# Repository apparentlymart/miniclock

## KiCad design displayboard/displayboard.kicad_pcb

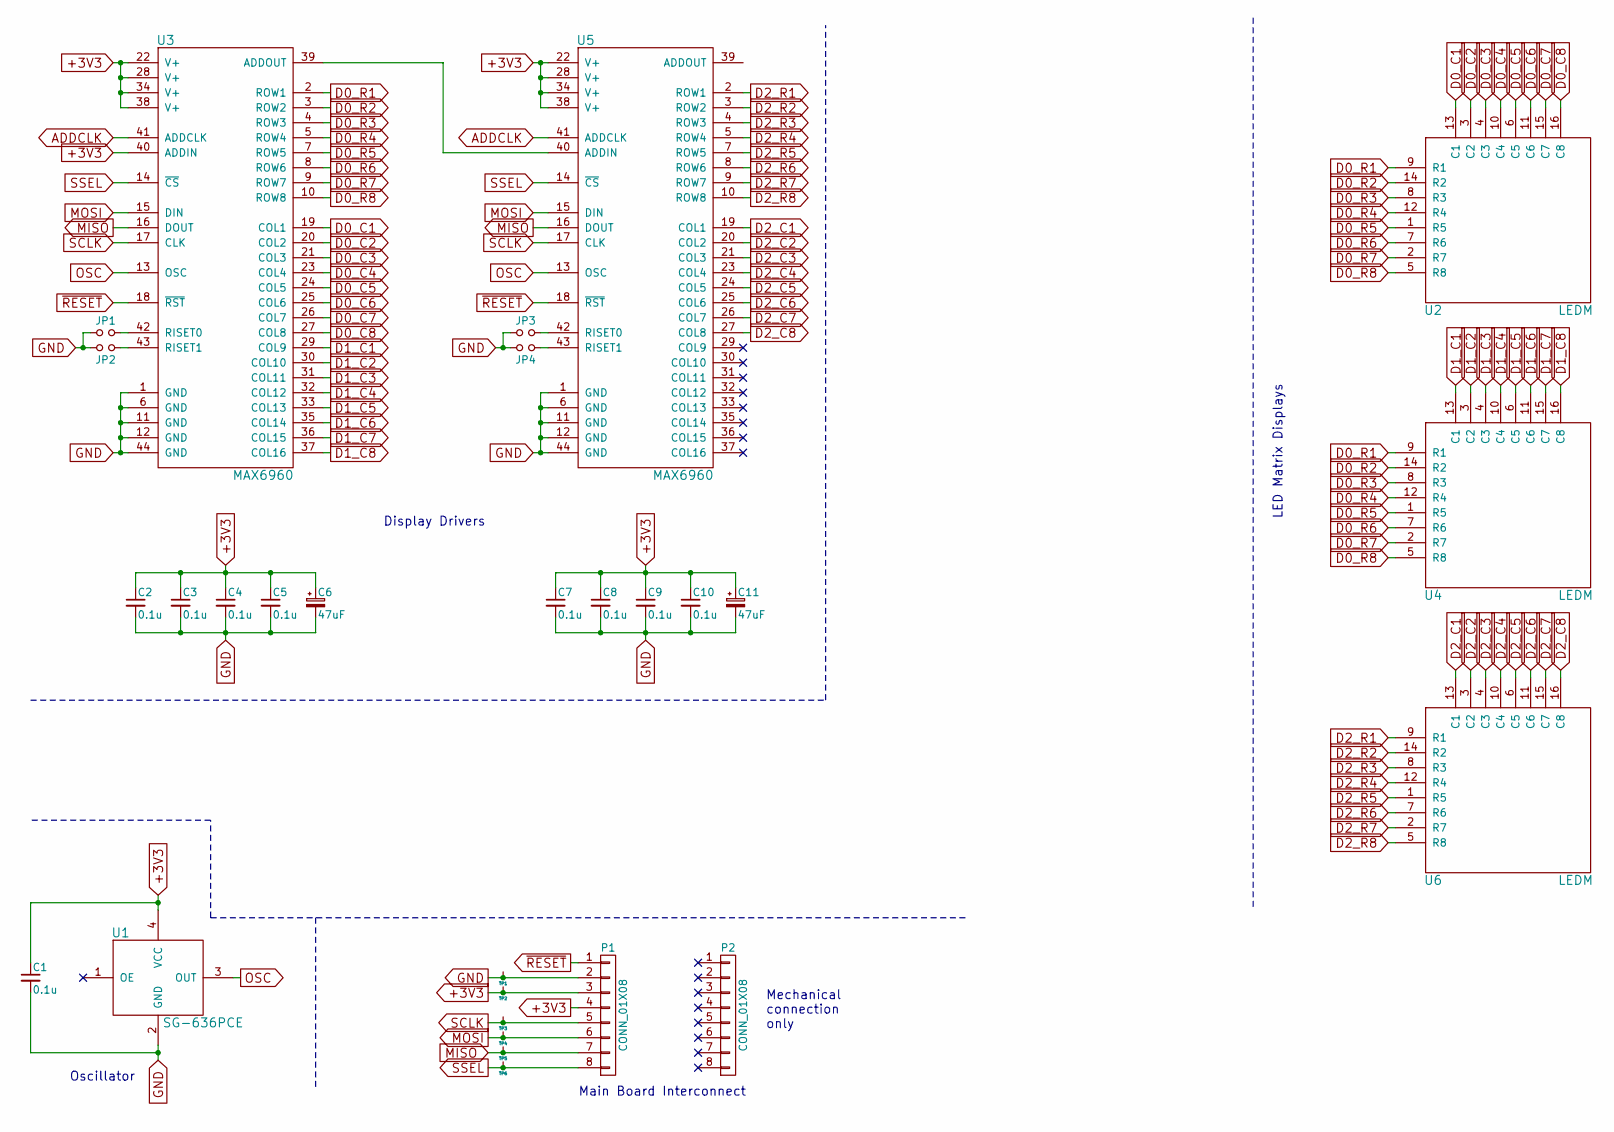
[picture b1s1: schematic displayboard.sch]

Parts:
C1, C2, C3, C4, C5, C7, C8, C9, C10: 0.1u; 0805
C6, C11: 47uF; UWX1V470MCL1GB
JP1, JP2, JP3, JP4: Jumper_NO_Small; 0805
P1, P2: CONN_01X08; Pin_Header_Straight_1x08
TP1, TP2, TP3, TP4, TP5, TP6: TESTPOINT
U1: SG-636PCE
U2, U4, U6: LEDM; KWM-R30881CUYB
U3, U5: MAX6960

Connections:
+3V3: C1.1, C2.1, C3.1, C4.1, C5.1, C6.1, C7.1, C8.1, C9.1, C10.1, C11.1, P1.3, P1.4, TP2.1, U1.4 (VCC), U3.22 (V+), U3.28 (V+), U3.34 (V+), U3.38 (V+), U3.40 (ADDIN), U5.22 (V+), U5.28 (V+), U5.34 (V+), U5.38 (V+)
ADDCLK: U3.41 (ADDCLK), U5.41 (ADDCLK)
D0_C1: U2.13 (C1), U3.19 (COL1)
D0_C2: U2.3 (C2), U3.20 (COL2)
D0_C3: U2.4 (C3), U3.21 (COL3)
D0_C4: U2.10 (C4), U3.23 (COL4)
D0_C5: U2.6 (C5), U3.24 (COL5)
D0_C6: U2.11 (C6), U3.25 (COL6)
D0_C7: U2.15 (C7), U3.26 (COL7)
D0_C8: U2.16 (C8), U3.27 (COL8)
D0_R1: U2.9 (R1), U3.2 (ROW1), U4.9 (R1)
D0_R2: U2.14 (R2), U3.3 (ROW2), U4.14 (R2)
D0_R3: U2.8 (R3), U3.4 (ROW3), U4.8 (R3)
D0_R4: U2.12 (R4), U3.5 (ROW4), U4.12 (R4)
D0_R5: U2.1 (R5), U3.7 (ROW5), U4.1 (R5)
D0_R6: U2.7 (R6), U3.8 (ROW6), U4.7 (R6)
D0_R7: U2.2 (R7), U3.9 (ROW7), U4.2 (R7)
D0_R8: U2.5 (R8), U3.10 (ROW8), U4.5 (R8)
D1_C1: U3.29 (COL9), U4.13 (C1)
D1_C2: U3.30 (COL10), U4.3 (C2)
D1_C3: U3.31 (COL11), U4.4 (C3)
D1_C4: U3.32 (COL12), U4.10 (C4)
D1_C5: U3.33 (COL13), U4.6 (C5)
D1_C6: U3.35 (COL14), U4.11 (C6)
D1_C7: U3.36 (COL15), U4.15 (C7)
D1_C8: U3.37 (COL16), U4.16 (C8)
D2_C1: U5.19 (COL1), U6.13 (C1)
D2_C2: U5.20 (COL2), U6.3 (C2)
D2_C3: U5.21 (COL3), U6.4 (C3)
D2_C4: U5.23 (COL4), U6.10 (C4)
D2_C5: U5.24 (COL5), U6.6 (C5)
D2_C6: U5.25 (COL6), U6.11 (C6)
D2_C7: U5.26 (COL7), U6.15 (C7)
D2_C8: U5.27 (COL8), U6.16 (C8)
D2_R1: U5.2 (ROW1), U6.9 (R1)
D2_R2: U5.3 (ROW2), U6.14 (R2)
D2_R3: U5.4 (ROW3), U6.8 (R3)
D2_R4: U5.5 (ROW4), U6.12 (R4)
D2_R5: U5.7 (ROW5), U6.1 (R5)
D2_R6: U5.8 (ROW6), U6.7 (R6)
D2_R7: U5.9 (ROW7), U6.2 (R7)
D2_R8: U5.10 (ROW8), U6.5 (R8)
GND: C1.2, C2.2, C3.2, C4.2, C5.2, C6.2, C7.2, C8.2, C9.2, C10.2, C11.2, JP1.1, JP2.2, JP3.1, JP4.2, P1.2, TP1.1, U1.2 (GND), U3.1 (GND), U3.6 (GND), U3.11 (GND), U3.12 (GND), U3.44 (GND), U5.1 (GND), U5.6 (GND), U5.11 (GND), U5.12 (GND), U5.44 (GND)
MISO: P1.7, TP5.1, U3.16 (DOUT), U5.16 (DOUT)
MOSI: P1.6, TP4.1, U3.15 (DIN), U5.15 (DIN)
unnamed: JP1.2, U3.42 (RISET0)
unnamed: JP2.1, U3.43 (RISET1)
unnamed: JP3.2, U5.42 (RISET0)
unnamed: JP4.1, U5.43 (RISET1)
unnamed: U3.39 (ADDOUT), U5.40 (ADDIN)
OSC: U1.3 (OUT), U3.13 (OSC), U5.13 (OSC)
SCLK: P1.5, TP3.1, U3.17 (CLK), U5.17 (CLK)
SSEL: P1.8, TP6.1, U3.14 (~CS), U5.14 (~CS)
~RESET: P1.1, U3.18 (~RST), U5.18 (~RST)

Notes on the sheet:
Mechanical connection only
Main Board Interconnect
Oscillator
LED Matrix Displays
Display Drivers

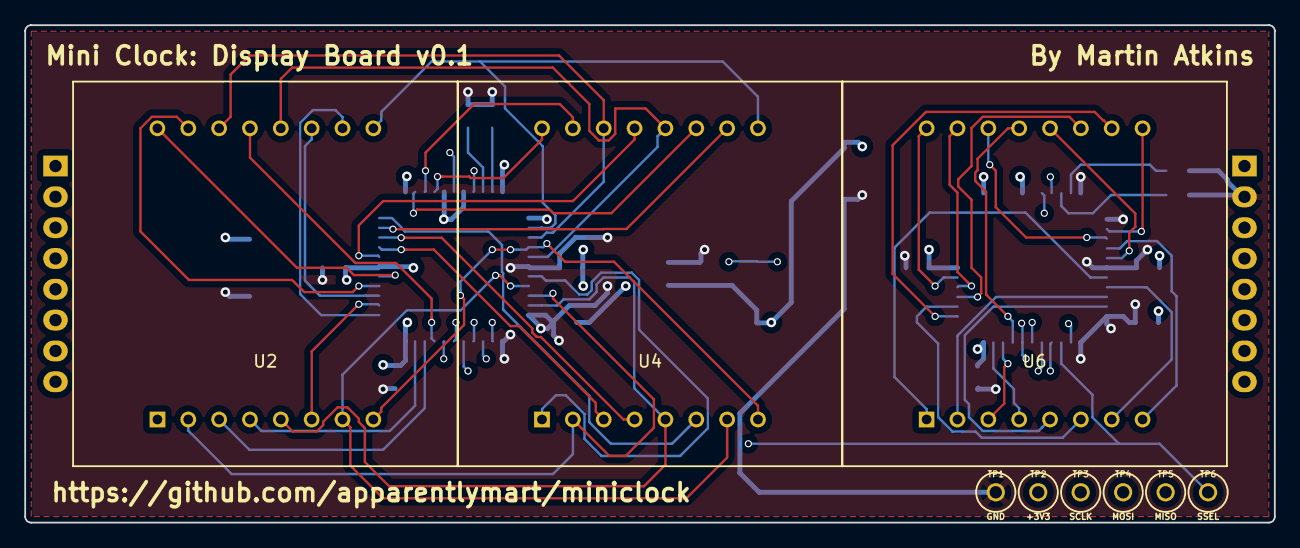
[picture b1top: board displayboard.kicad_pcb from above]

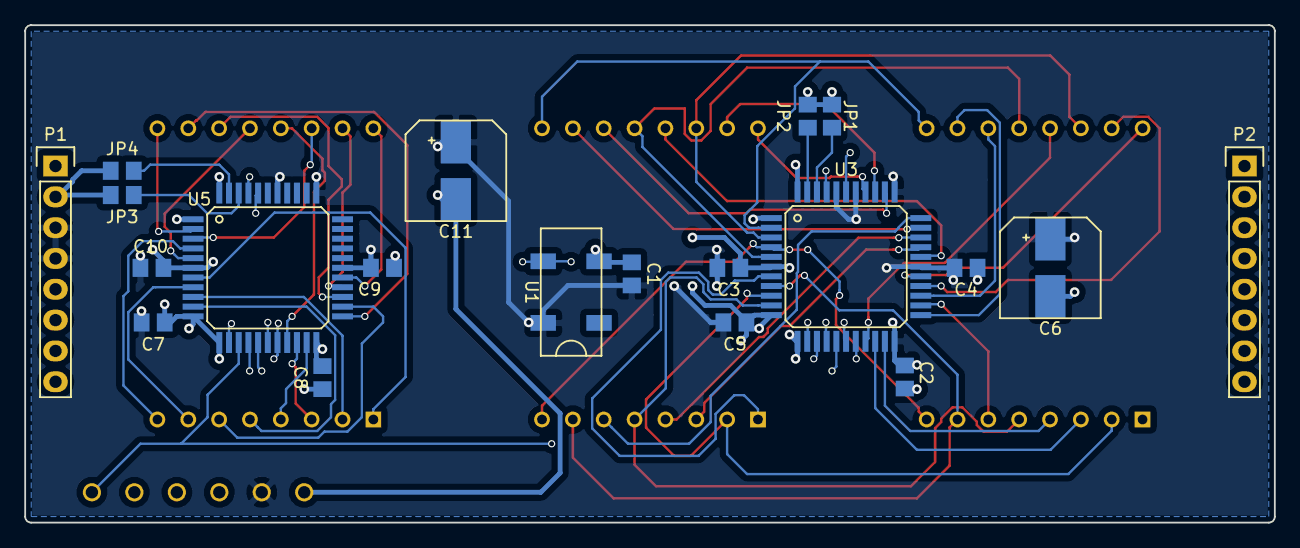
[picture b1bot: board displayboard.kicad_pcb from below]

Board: 4 copper layers, 103.0 x 41.0 mm, 29 parts (20 on the bottom side), 54 nets.

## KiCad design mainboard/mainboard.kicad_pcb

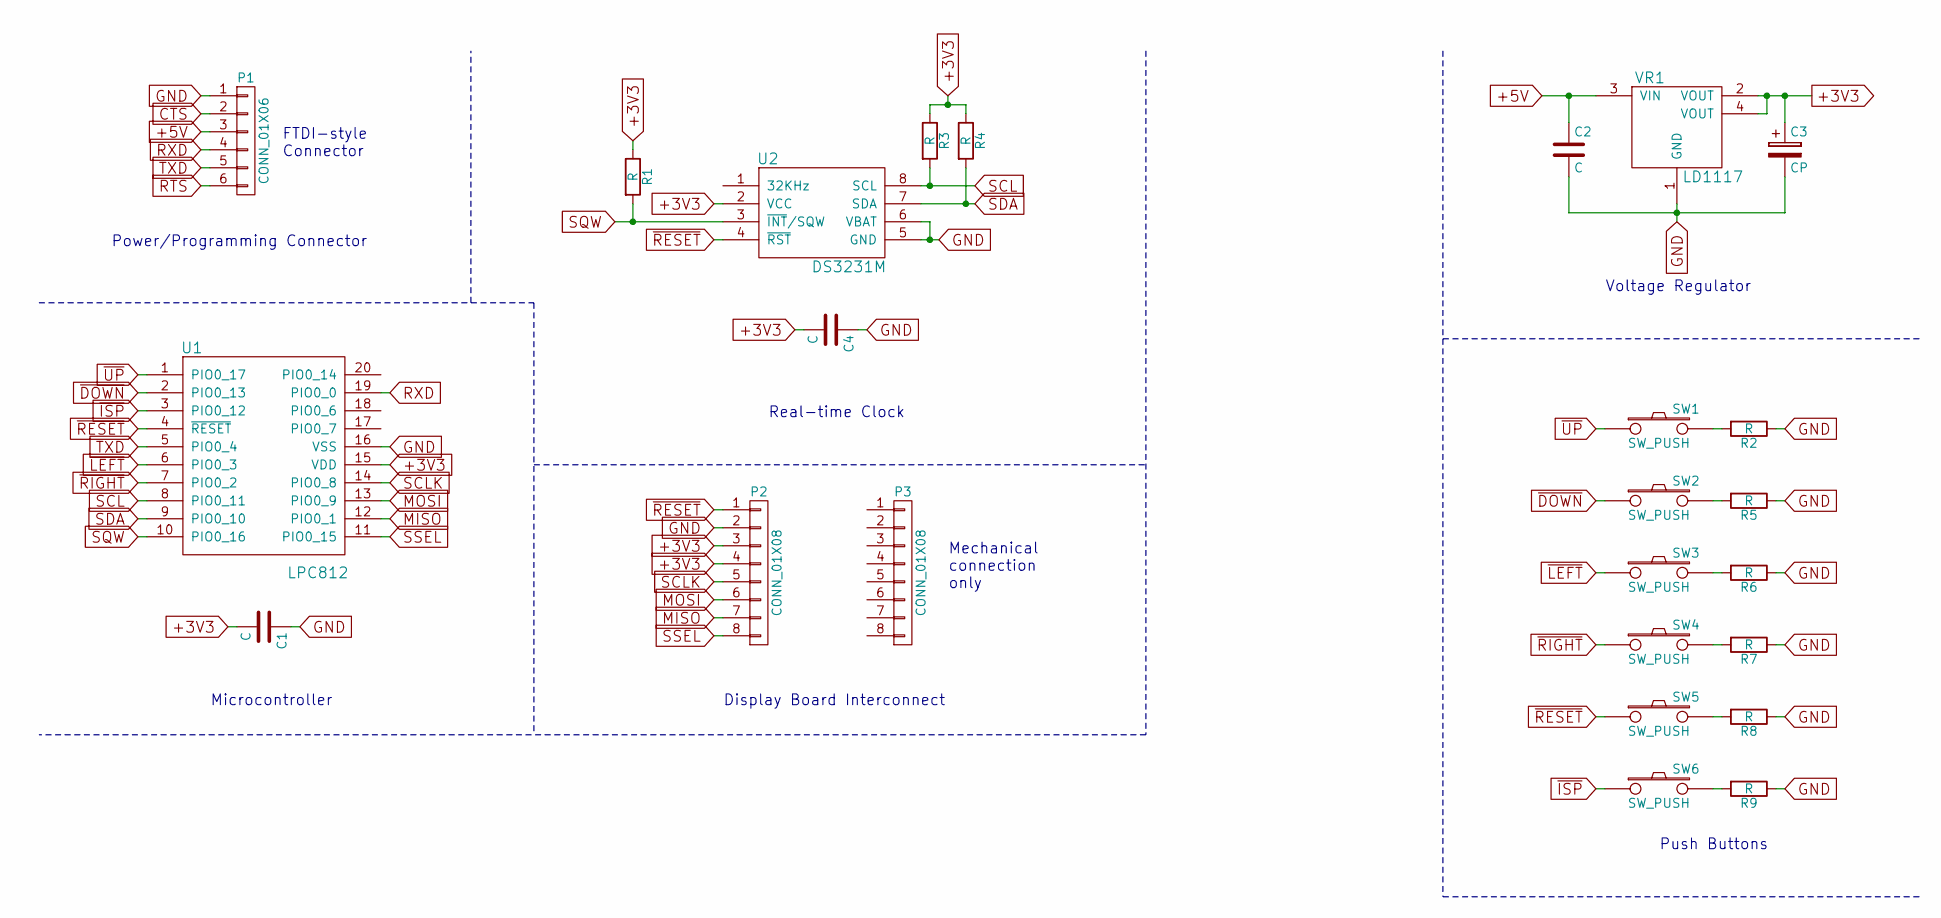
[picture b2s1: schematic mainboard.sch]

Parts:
C1, C2, C4: C; C_0805_HandSoldering
C3: CP; CPOL_SMD_6.3mm
P1: CONN_01X06; Pin_Header_Straight_1x06
P2, P3: CONN_01X08; Pin_Header_Straight_1x08
R1, R2, R3, R4, R5, R6, R7, R8, R9: R; R_0805_HandSoldering
SW1, SW2, SW3, SW4, SW5, SW6: SW_PUSH; PUSHSWITCH
U1: LPC812; SOIC-20_7.5x12.8mm_Pitch1.27mm
U2: DS3231M; SOIC-8_3.9x4.9mm_Pitch1.27mm
VR1: LD1117; SOT223

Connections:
+3V3: C1.2, C3.1, C4.2, P2.3, P2.4, R1.1, R3.1, R4.1, U1.15 (VDD), U2.2 (VCC), VR1.2 (VOUT), VR1.4 (VOUT)
+5V: C2.1, P1.3, VR1.3 (VIN)
CTS: P1.2
GND: C1.1, C2.2, C3.2, C4.1, P1.1, P2.2, R2.1, R5.1, R6.1, R7.1, R8.1, R9.1, U1.16 (VSS), U2.5 (GND), U2.6 (VBAT), VR1.1 (GND)
MISO: P2.7, U1.12 (PIO0_1)
MOSI: P2.6, U1.13 (PIO0_9)
unnamed: R2.2, SW1.2
unnamed: R5.2, SW2.2
unnamed: R6.2, SW3.2
unnamed: R7.2, SW4.2
unnamed: R8.2, SW5.2
unnamed: R9.2, SW6.2
RTS: P1.6
RXD: P1.4, U1.19 (PIO0_0)
SCL: R3.2, U1.8 (PIO0_11), U2.8 (SCL)
SCLK: P2.5, U1.14 (PIO0_8)
SDA: R4.2, U1.9 (PIO0_10), U2.7 (SDA)
SQW: R1.2, U1.10 (PIO0_16), U2.3 (~INT~/SQW)
SSEL: P2.8, U1.11 (PIO0_15)
TXD: P1.5, U1.5 (PIO0_4)
~DOWN: SW2.1, U1.2 (PIO0_13)
~ISP: SW6.1, U1.3 (PIO0_12)
~LEFT: SW3.1, U1.6 (PIO0_3)
~RESET: P2.1, SW5.1, U1.4 (~RESET), U2.4 (~RST)
~RIGHT: SW4.1, U1.7 (PIO0_2)
~UP: SW1.1, U1.1 (PIO0_17)

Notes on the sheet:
FTDI-style Connector
Microcontroller
Real-time Clock
Voltage Regulator
Power/Programming Connector
Mechanical connection only
Display Board Interconnect
Push Buttons

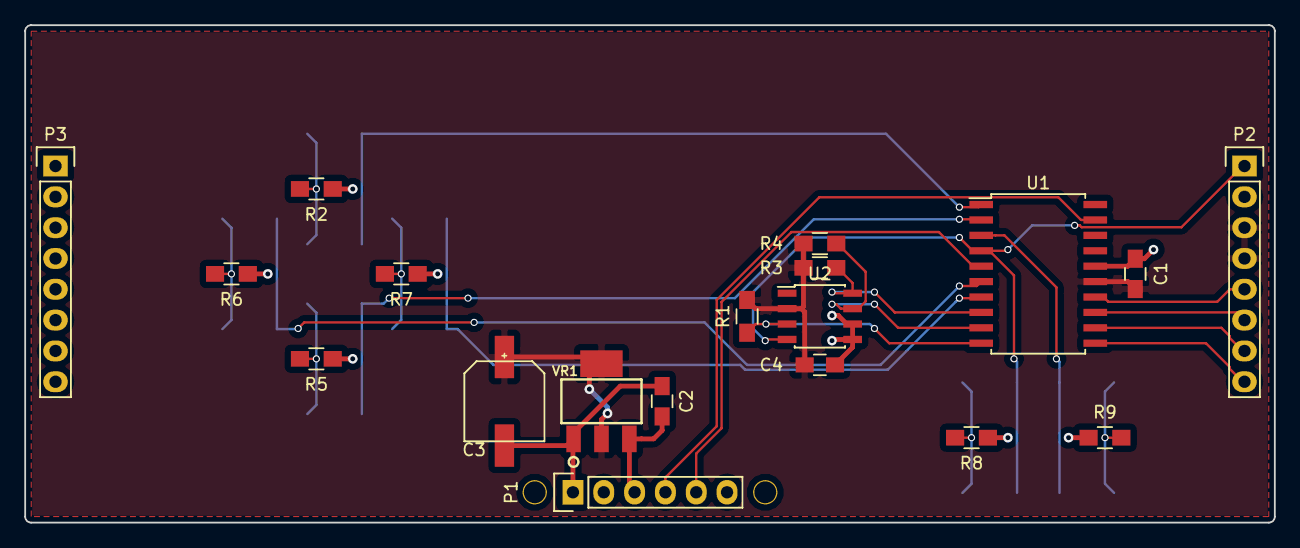
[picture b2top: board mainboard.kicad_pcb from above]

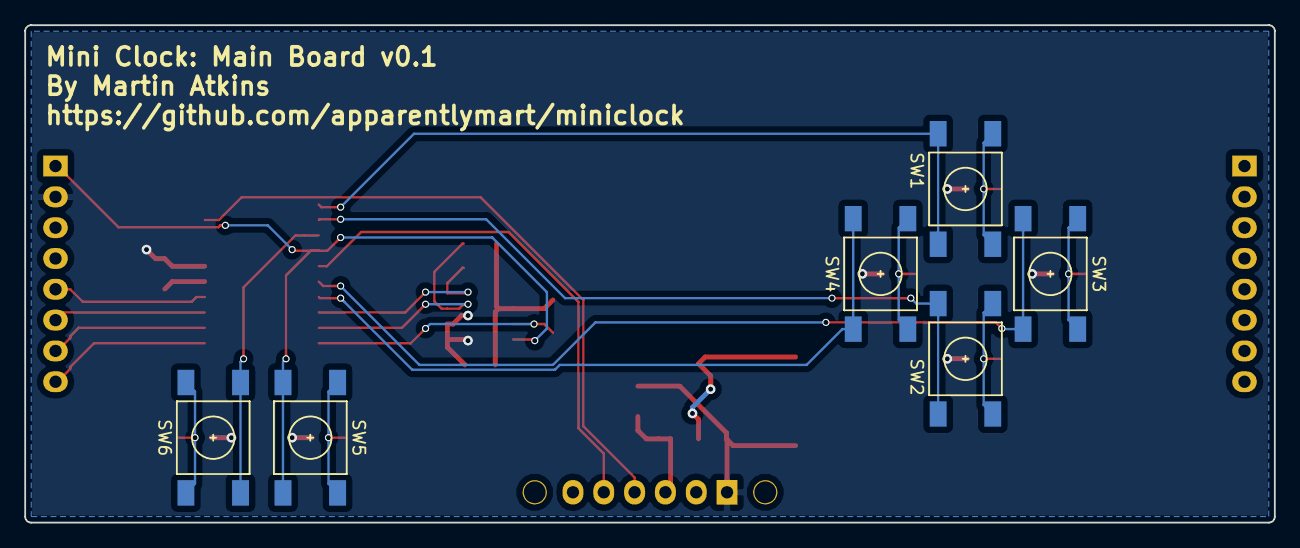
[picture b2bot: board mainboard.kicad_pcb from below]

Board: 2 copper layers, 103.0 x 41.0 mm, 25 parts (6 on the bottom side), 24 nets.

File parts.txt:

RTC:
http://www.digikey.com/product-detail/en/DS3231MZ%2B/DS3231M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

LPC812 Microcontroller:
http://www.digikey.com/product-detail/en/LPC812M101JD20FP/56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

Right-angle header (for FTDI serial cable):
http://www.digikey.com/product-detail/en/0901210126/WM8100-N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

Square 1.2" LED matrix:
http://www.adafruit.com/products/1819

LED Matrix Driver
http://www.digikey.com/product-detail/en/MAX6960AMH%2BD/MAX6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

3.3V voltage regulator
http://www.digikey.com/product-detail/en/LD1117S33TR/497-124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

6 Buttons:
http://www.digikey.com/product-detail/en/FSM4JSMATR/450-1759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

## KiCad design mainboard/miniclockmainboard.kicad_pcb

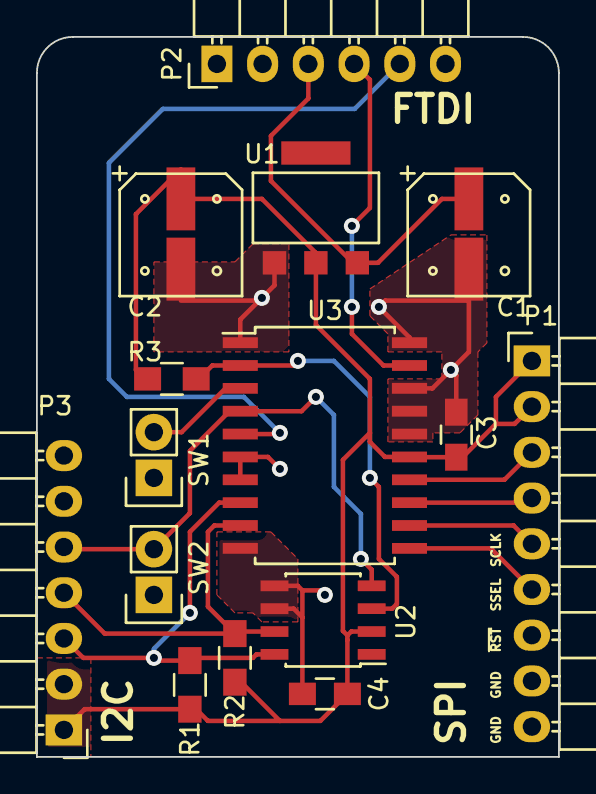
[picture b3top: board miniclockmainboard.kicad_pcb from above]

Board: 2 copper layers, 29.0 x 40.0 mm, 15 parts (0 on the bottom side), 14 nets.

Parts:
C1, C2: 10uF; Nichicon_PolCap_6.3
C3, C4: 0.1uF; C_0805_HandSoldering
P1: CONN_9; Pin_Header_Angled_1x09
P2: CONN_6; Pin_Header_Angled_1x06
P3: CONN_7; Pin_Header_Angled_1x07
R1, R2, R3: 10k; R_0805_HandSoldering
SW1, SW2: SW_PUSH; Pin_Header_Straight_1x02
U1: LD1117; SOT-223
U2: DS3231M; SOIC-8_3.9x4.9mm_Pitch1.27mm
U3: LPC812M101JD20; SOIC-20_7.5x12.8mm_Pitch1.27mm

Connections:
/1HZ: R3.2, U2.3, U3.2
/+5V: C1.1, P2.3, U1.3
/MISO: P1.4, U3.13
/MOSI: P1.3, U3.14
/RXD: P2.5, U3.5
/SCL: P3.3, R1.2, U2.8, U3.8
/SCLK: P1.5, U3.12
/SDA: P3.4, R2.2, U2.7, U3.9
/SSEL: P1.6, U3.11
/TXD: P2.4, U3.19
/~RST: P1.7, P3.5, SW2.2, U2.4, U3.4
GND: C1.2, C2.2, C3.2, C4.1, P1.8, P1.9, P2.1, P3.6, P3.7, SW1.1, SW2.1, U1.1, U2.5, U2.6, U3.1, U3.6, U3.7, U3.10, U3.16, U3.17, U3.18, U3.20
unnamed: SW1.2, U3.3
VCC: C2.1, C3.1, C4.2, P1.1, P1.2, P3.1, P3.2, R1.1, R2.1, R3.1, U1.2, U2.2, U3.15

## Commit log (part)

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2015-02-23 Sketch BOM
2015-02-28 Update the parts list.
2015-02-28 KiCAD project.
2015-02-28 Initial import of schematic, with voltage regulator.
2015-02-28 Basic wiring for MCU and RTC.
    Still need to add capacitors to the power inputs.
2015-03-28 Local eeschema library, starting with LCP812 symbol.
2015-03-28 Start of schematic for the main control board.
2015-03-28 Further work on the main board schematic.
2015-03-28 Complete first rev of the main board schematic.
2015-03-28 Some PCB footprints for the main board.
2015-03-28 Schematic to footprint mappings.
2015-03-28 Main board PCB layout.
2015-03-28 Add some silkscreen captions to the rear of the main board.
2015-03-29 Shrink the main board width.
    Previous version was slightly too wide for the first prototype's
    enclosure. The new size is much smaller than the available space in the
    enclosure.
2015-03-29 Fix up the pad positions on the polarized caps.
    The pads were incorrectly spaced before since the space between the pad
    edges was confused with the space between the centers.
2015-09-08 Delete everything so we can start over.
    This project has bitrotted since I last opened it, so rather than trying
    to repair it I'm just going to start over again.
2015-09-08 Map schematic symbols to footprints.
2015-09-08 Mainboard outline
2015-09-08 Component placement on PCB.
2015-09-08 Random schematic editor settings.
2015-09-08 DC regulator traces.
2015-09-08 Button traces.
2015-09-08 RTC traces.
2015-09-08 Remaining traces.
2015-09-08 Connect final missing link.
    (This isn't actually really needed since these things are connected
    internally within the regulator, but this pacifies the KiCad DRC.
2015-09-08 Using a larger LED matrix now.
    Going bigger because it'll be easier to fit the LED matrix drivers on the
    display board this way. It isn't really necessary for the mainboard to be
    this large except that it ought to match the display board.
2015-10-18 First steps towards a firmware.
    This builds and runs but doesn't quite work yet... the UART seems to be
    running faster than desired, causing every alternating character to be
    missed by the receiving device.
2015-10-26 Don't run lpc21isp with sudo.
    Now got udev rules set up properly for this, so don't need it on my
    machine and it's a bad idea in general anyway.
2015-10-26 Header guards on lpc812.h and serial.h.
2015-10-26 Use the PLL for the main clock.
    This allows us to run at 60MHz.
2015-10-26 Print newline at the end of our message.
2015-10-26 Poll indefinitely for USART RX to become available.
    Also wait for it to return to idle after each character. This isn't
    strictly necessary but it keeps things easier for debugging for the
    moment.
2015-10-30 Explicitly set the system clock to 60MHz.
    In spite of the earlier comment to the contrary, this was actually already
    the case because that's the boot-time setting. Here we just correct the
    comment and add an explicit configuration to aid in understanding of
    what's going on here.
2015-10-30 Correctly configure the UART.
    Some mis-reading of the datasheet led to a complete misunderstanding of
    the structure of the USART0_CFG register, causing the UART to be
    configured for 2 stop bits, 7-bit data length and even parity. Despite
    how wrong this was, it ended up generating a bunch of bytes correctly,
    making it hard at first to recognize the problem.
    The new setting is, as the comment originally suggested, 1 stop bit,
2015-11-02 Basic prototype of using pin interrupts.
    Still doesn't do anything useful, but this is a reasonable checkpoint
    on the way to having a button driver.
2015-11-06 Use C11 standard when compiling.
2015-11-06 Use udev alias /dev/miniclock for programming.
2015-11-06 Blocking I2C driver.
    Will rewrite this to be interrupt-driven later, but this is just a simple
    case to prove that the RTC chip is behaving.
2015-11-06 Sleep and use the RTC's 1Hz square wave to wake up every 0.5s.
    Still just more prototyping, in this case making sure that we can use the
    1Hz SQW pin as an interrupt and sleep between them.
2015-11-06 Start stubbing out the scheduler interface.
2015-11-08 Link with gcc so we can include libgcc.
2015-11-08 Add some interrupt vectors that were skipped.
    All of the interrupt vectors above 12 were off by three, which explains
    why the GPIO interrupts didn't seem to be working quite right before.
2015-11-08 Wake-up timer registers.
2015-11-08 PMU registers.
2015-11-08 Fleshed out scheduler.
    It now basically works and supports timer events. It's using the
    SysTick timer, so we run through the event loop at least once every
    10ms.
    Ideally we would set the timer to occur at the time of the next timer
    in the list, but so far I couldn't find a way to measure the time
    elapsed while the processor is asleep and so waking up every 10ms is
2015-11-08 Timer task list should be in order of wake_time.
    Previously I cheated and just appended each new task to the end of the
    list, since I knew the test code only had one task at a time. This is the
    more correct implementation, inserting the new task into the appropriate
    place in the list.
2015-11-08 Use macros to make task implementations less verbose.
    This borrows from Adam Dunkels' protothreads, but using the GCC computed
    goto extension to avoid the limitations around using switch statements.
2015-11-08 uart_println_int_hex wrapper to print a captioned integer.
2015-11-08 UI state machine represented as a DOT graph.
2015-11-09 UI state machine.
    Handles the transitions between the UI states when the directional buttons
    are pressed.
2015-11-09 Put the ui_state enum in the header, not the module.
2015-11-09 Start of display-handling code.
    The display module is responsible for rendering something appropriate
    on the screen for the current state, and creating animated transitions
    between states.
2015-11-09 Don't lock up when multiple timer tasks are outstanding.
    This loop was broken in that it would lock up if it needed to insert
    a new task after an existing task, because the loop iteration expression
    was incorrect.
2015-11-09 Export the millis count for use in other modules.
2015-11-09 Remove incorrect comment about deadlock.
    This claimed that having no runnable tasks was a deadlock, but that's
    incorrect: no runnable tasks can just mean that we're waiting for events
    to occur before any tasks become runnable.
2015-11-09 Further progress on the transition animations.
2015-11-09 Prototype display driver.
    The display is built from "display elements", which are defined by a
    row generator function and an integer argument to provide to it. Each
    element can generate zero or more display rows (which will actually be
    columns on the final display).
    Eventually each UI state will have its own set of display elements that
    together define what is displayed on-screen in that state. The display
2015-11-14 Render both states when transitioning horizontally.
2015-11-14 Vertical transitions
2015-11-14 Generalize the offset animation to work in all directions.
    The previous prototype had a separate-but-largely-identical implementation
    for each movement direction. Here we generalize this to a single
    implementation that just shifts the offset towards a target.
2015-11-14 Select display elements based on state.
    Initially we just show the HH:MM placeholder for the TIME_HM state and
    blank for everything else.
    This has exposed a bug in the horizontal-offset display rendering code
    which needs further investigation.
2015-11-14 Keep track of real time and update display each time it changes.
    We actually keep track of time to the half-second so that we can blink
    display elements on and off at 1Hz in synchrony with the RTC's idea
    of seconds.
2015-11-14 Allow display elements to blink.
    When the blink flag is set, the element's rows are rendered as blank
    during the second half of every second, but the element still takes up
    the same amount of space.
2015-11-15 Introduce an "elastic space" animation mode.
    This allows some simple transitions that do not require the entire screen
    to move at once, but instead allow a gap to be introduced into the display
    whose size can be animated over time.
2015-11-15 main.c explicitly depends on clock.h.
2015-11-15 TomThumbTall characters and "Set Time"/"Set Date" menu items.
2015-11-15 Flip the animation directions.
    Previously the whole-screen transitions went in opposition to the
    direction arrows, as if moving the "camera" over a set of items, while
    the hour-to-second transition was the opposite.
    For consistency, now the animation moves in the direction of the arrow
    pressed, as if the user is moving a "canvas" that all of the UI elements
    are on.
2015-11-15 UI states for setting the time.
    This UI is not actually functional yet, but it shows the right stuff on
    the screen so that it'll work once we get the time-updating functions
    wired up.
2015-11-15 UI for setting the time actually works.
    The hour, minute and second can now be set via the UI.
2015-11-15 Eliminate the transition debugging output.
    The UART now just produces the emulated display.
2015-11-22 Start of display board design.
    So far just enough to conform to the shape and connector layout of the
    main board.
2015-11-23 MAX6960 schematic symbol.
2015-11-29 SG-636PCE oscillator schematic symbol.
2015-11-29 Complete schematic.
2015-11-29 MAX6960 footprint
2015-11-29 SG-636PCE footprint
2015-11-29 Assorted updates that I didn't properly distinguish.
2015-11-29 PCB footprint assignment and floor planning.
2015-11-29 Spinning the chips around trying to find the least-sucky orientation.
    There seems to be no good orientation for these chips vs. the pinout of
    the LED displays.
2015-11-29 Connect the bulk capacitor.
2015-12-27 Another attempt at PCB traces.
    This became kinda spaghetti-like but I think it should be okay since none
    of these signals are high-frequency. The power planes got a bit abused for
    some signal routing but hopefully not too much.
2015-12-27 3D models of some of the components.
    Also flipped the inter-board connection headers since they were on the
    wrong side of the board as far as KiCad is concerned.
2015-12-27 Label the test points.
2015-12-28 Shrink solder mask clearance on the QFP chips.
    Their pin pitch is too low for the default clearance, causing there to be
    no solder mask between the pins at all. This shrinks it so that there is
    at least a small amount of clearance.
2015-12-28 View all the layers.
2016-01-31 Latest PCB changes
2016-01-31 Note on which capacitors and oscillators are being used
2016-02-01 Not-yet-working SPI driver
    There is something missing from this but I've not yet figured out what.
2016-02-01 OpenOCD config to debug the MCU with a j-link.
2016-02-01 Stop using GPIO 1 and 15 as debug signals
    We're now going to use them for SPI.
2016-02-01 Software SPI implementation
    Couldn't quite figure out why the hardware SPI wasn't playing ball so I
    just wrote a bit-bang software implementation for now. Will probably come
    back and try to get hardware SPI working again once the rest is
    implemented.
2016-02-01 init.c depends on uart_println for exception handling
2016-02-01 Render display to LED matrices rather than UART
    Now that we have working SPI we can talk to the display drivers and
    actually render the display on the display.
